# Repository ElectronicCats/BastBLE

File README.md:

# Bast BLE

Bast BLE is all the best in the world format Feather and BLE with a Nordic NRF!, Feather pin to pin compatible with a USB port type C.

Bast-BLE is supported in the Arduino development environment and Circuit Python coming soon

We love all our Feathers equally, but this Feather is very special. It's our first Feather that is specifically designed for use with CircuitPython! CircuitPython is our beginner-oriented flavor of MicroPython - and as the name hints at, its a small but full-featured version of the popular Python programming language specifically for use with circuitry and electronics.

Please note, CircuitPython does not come preloaded. See the full guide linked below for instructions on installing it

Lipoly battery and USB cable not included (but we do have lots of options in the shop if you'd like!)

## Hardware Features

* Nordic nRF52840 System-on-Chip
	- ARM® Cortex®-M4F processor optimized for ultra-low power operation
	- Combining *Bluetooth 5*, *Bluetooth Mesh*, *Thread*, *IEEE 802.15.4*, *ANT* and *2.4GHz proprietary*
	- On-chip NFC-A tag
	- On-chip USB 2.0 (Full speed) controller
	- ARM TrustZone® Cryptocell 310 security subsystem
	- 1 MB FLASH and 256 kB RAM
* Program/Debug options with DAPLink
	- MSC - drag-n-drop programming flash memory
	- CDC - virtual com port for log, trace and terminal emulation
	- HID - CMSIS-DAP compliant debug channel
	- WEBUSB HID - CMSIS-DAP compliant debug channel
* External ultra-low power 64-Mb QSPI FLASH memory
* Up to 21 GPIOs available via headers
* IF Boot/Reset Button
* On-board 2.4G chip antenna 
* 3.3V regulator with 1A peak current output
* VBUS & VIN Power-Path Management
* Reversible USB 3.1 Type-C Connector
* Breadboard-friendly with dual 18-Pin headers
* Feather Format

## How to get Bast BLE
Bast BLE is available on the following channels (click to go directly to the product):

## Pinout Diagram
Coming Soon..

## Software Resource

The nRF52840 Micro Dev Kit USB Dongle can be used to play with : *nRF5 SDK*, *OpenThread*, *Web Bluetooth*, *iBeacon*, *Eddystone*, and more.

| Software  | Brief Description |
| ---------- | ----- |
| [Arduino Core MbedOS](https://github.com/ElectronicCats/ArduinoCore-mbed) | The friendly Arduino core by Electronic Cats with MbedOS, |
| [UF2 Bootloader](https://github.com/ElectronicCats/Adafruit_nRF52_Bootloader) | UF2 Bootloader fir NRF52, |
| [nRF5 SDK](nrf5-sdk/) | Offical Software Development Kit for nRF51 and nRF52 Series |
| [OpenThread Border Router](OTBR/) | An open source border router, designed to work with OpenThread |
| [Thread Network Sniffer](thread-sniffer/) | Help you to efficiently analyze Thread network traffic|
| [Web Bluetooth](https://webbluetoothcg.github.io/web-bluetooth/) | Bluetooth support for the Web |
| [iBeacon](https://developer.apple.com/ibeacon/) | A Bluetooth low energy advertising message format designed by Apple |
| [Eddystone](https://github.com/google/eddystone) | A protocol specification that defines a Bluetooth low energy message format for proximity beacon messages |
| [CircuitPython](https://github.com/adafruit/circuitpython/blob/master/ports/nrf/README.md) | A Python language for microcontrollers designed to simplify experimentation and learning |
| [TinyGo](https://github.com/tinygo-org/tinygo) | Go compiler for small devices, based on LLVM |
| [Rust for nrf52840-mdk](https://github.com/nrf-rs/nrf52840-mdk-rs) | Rust support for the nrf52840-mdk development board |
| [RIOT OS](https://github.com/RIOT-OS/RIOT/blob/695e91a90a6545b6937bd0f52f0e87d278155ec0/boards/nrf52840-mdk/doc.txt) | The friendly Operating System for the Internet of Things, |

## Contributing

We would love for you to contribute to this project and help make it even better than it is today! 

License

Electronic Cats invests time and resources providing this open source design, please support Electronic Cats and open-source hardware by purchasing products from Electronic Cats!

Designed by Electronic Cats.

Firmware released under an GNU AGPL v3.0 license. See the LICENSE file for more information.

Hardware released under an CERN Open Hardware Licence v1.2. See the LICENSE_HARDWARE file for more information.

Electronic Cats is a registered trademark, please do not use if you sell these PCBs.

January 2020

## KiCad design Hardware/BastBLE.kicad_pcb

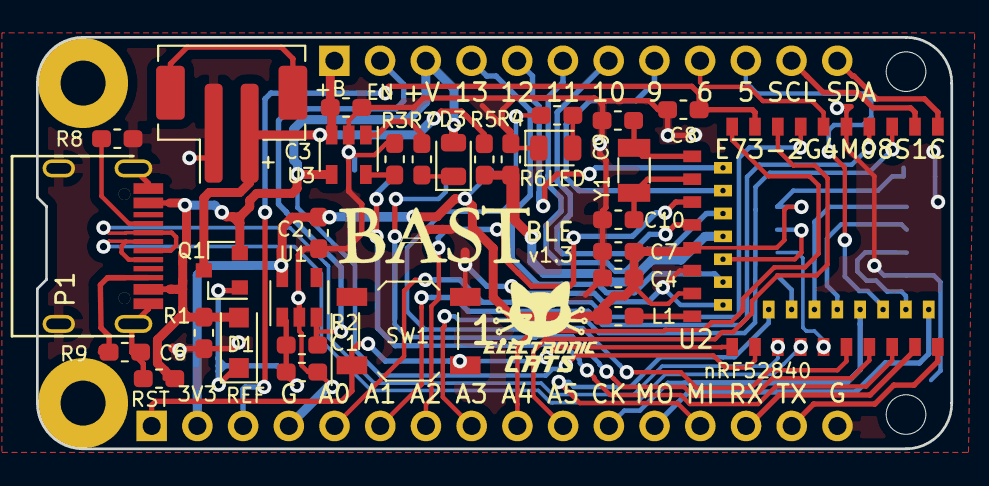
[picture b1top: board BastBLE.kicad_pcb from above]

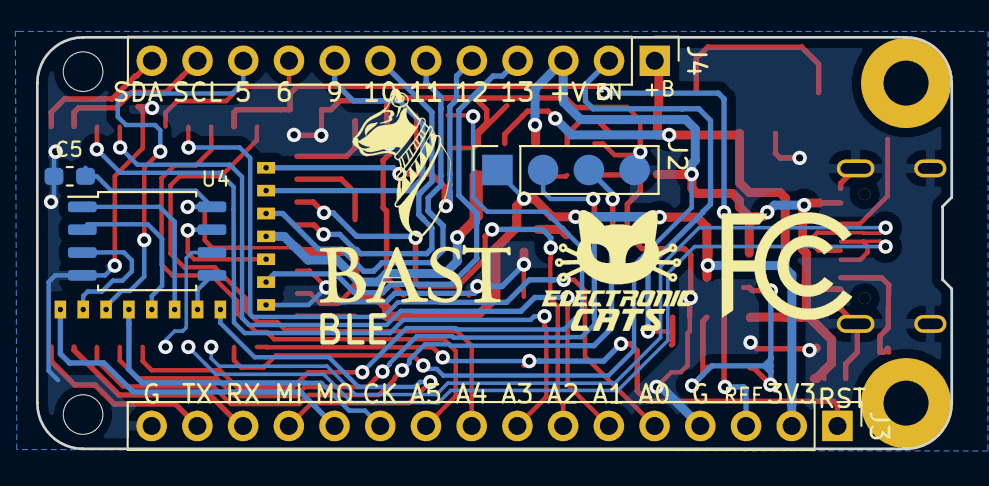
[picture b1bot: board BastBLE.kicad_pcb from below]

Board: 2 copper layers, 50.8 x 22.9 mm, 35 parts (5 on the bottom side), 49 nets.

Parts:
C1, C2, C3: 10uF; C_0603_1608Metric_Pad1.05x0.95mm_HandSolder
C4, C5, C6, C7, C8: 0.1uF; C_0603_1608Metric_Pad1.05x0.95mm_HandSolder
C9, C10: 22pF; C_0603_1608Metric_Pad1.05x0.95mm_HandSolder
D1: MBR120; D_SOD-123F
D2, D3: LED; LED_0805_2012Metric
J1: Conn_Battery; JST_PH_B2B-PH-SM4-TB_1x02-1MP_P2.00mm_Vertical
J2: SWD; PinSocket_1x04_P2.54mm_Vertical
J3: Conn_left; PinHeader_1x16_P2.54mm_Vertical
J4: Conn_right; PinHeader_1x12_P2.54mm_Vertical
L1: 10uH; L_0603_1608Metric_Pad1.05x0.95mm_HandSolder
P1: USB_C_Plug_USB2.0; C393939
Q1: DMG3415U-7; SOT-23
R1, R2, R5, R6: 100K; R_0603_1608Metric_Pad1.05x0.95mm_HandSolder
R3: 4K7; R_0603_1608Metric_Pad1.05x0.95mm_HandSolder
R4, R7: 1K; R_0603_1608Metric_Pad1.05x0.95mm_HandSolder
R8, R9: 5K1; R_0603_1608Metric_Pad1.05x0.95mm_HandSolder
SW1: RESET; SW_SPST_TL3342
U1: AP2112K-3.3; SOT-23-5
U2: E73-2G4M08S1C; E73-2G4M08S1C-52840
U3: MCP73831-2-OT; SOT-23-5
U4: W25Q32JVSS; SOIC-8_5.23x5.23mm_P1.27mm
Y1: 32Khz; Crystal_SMD_3215-2Pin_3.2x1.5mm

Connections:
+3V3: C2.1, C4.1, C5.1, C7.1, J2.1, J3.2, L1.1, U1.5, U2.19, U2.23, U4.8
+BATT: C3.2, J1.2, J4.1, Q1.3, R5.1, U3.3
/A0: J3.5, U2.7
/A1: J3.6, U2.4
/A2: J3.7, U2.15
/A3: J3.8, U2.3
/A4: J3.9, U2.10
/A5: J3.10, U2.8
/AREF: C8.1, J3.3, U2.9
/D5: J4.10, U2.38
/D6: J4.9, U2.6
/D9: J4.8, U2.14
/D10: J4.7, U2.17
/D11: J4.6, U2.16
/D12: J4.5, U2.12
/D13: J4.4, U2.22
/D+: P1.A6, U2.31
/D-: P1.A7, U2.29
/EN: J4.2, R2.2, U1.3
/LED: R4.1, U2.35
/MISO: J3.13, U2.28
/MOSI: J3.12, U2.42
/QSPI_CS: U2.32, U4.1
/QSPI_DATA0: U2.30, U4.5
/QSPI_DATA1: U2.34, U4.2
/QSPI_DATA2: U2.40, U4.3
/QSPI_DATA3: U2.20, U4.7
/QSPI_SCK: U2.33, U4.6
/RST: J3.1, SW1.2, U2.26
/RX: J3.14, U2.41
/SCK: J3.11, U2.36
/SCL: J4.11, U2.2
/SDA: J4.12, U2.1
/SWCLK: J2.3, U2.39
/SWDIO: J2.2, U2.37
/TX: J3.15, U2.43
/VBAT: R5.2, R6.1, U2.18
GND: C1.2, C2.2, C3.1, C4.2, C5.2, C6.2, C7.2, C8.2, C9.2, C10.2, D2.1, J1.1, J2.4, J3.4, J3.16, P1.A1, P1.S1, R1.2, R3.2, R6.2, R8.1, R9.1, SW1.1, U1.2, U2.5, U2.21, U2.24, U3.2, U4.4
unnamed: C1.1, D1.1, Q1.1, R2.1, U1.1
unnamed: C9.1, U2.11, Y1.1
unnamed: C10.1, U2.13, Y1.2
unnamed: D2.2, R4.2
unnamed: D3.1, R7.1
unnamed: L1.2, U2.25
unnamed: P1.A5, R8.2
unnamed: P1.B5, R9.2
unnamed: R3.1, U3.5
unnamed: R7.2, U3.1
VBUS: C6.1, D1.2, D3.2, J4.3, P1.A4, Q1.2, R1.1, U2.27, U3.4

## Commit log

2020-01-23 schematic
2020-01-23 add gitignore
2020-02-01 assigned pinout complete
2020-02-01 SWD pinout ok, assigned mosfet
2020-02-09 Format adafruit in PCB, init BOM
2020-02-11 init assignament footprints
2020-02-19 Review PCB
2020-03-14 change L1 package
2020-03-26 fix failed components and tracks
2020-03-27 routeo signals
2020-03-28 Communication miso, mosi, tx, rx
2020-03-30 Routeo a4 a5, fix sck mosi
2020-03-30 fix c8, r6, and pin
2020-03-31 D11-SDA
2020-04-14 change pins schematic
2020-04-15 change routeo
2020-04-20 routeo D
2020-04-22 chenge analog signals routeo
2020-04-23 A0 rf
2020-04-24 erase traces, add note
2020-04-24 add crystal and fix analogs
2020-05-04 add footprint and netlist
2020-05-05 fix components
2020-05-05 C6 VBUS
2020-05-06 D- D+
2020-05-07 Flash memory
2020-05-07 change pin SDA SCL
2020-05-08 fix traces
2020-05-08 tracks u2
2020-05-08 VBUS and batt
2020-05-12 A1 change cap vbus
2020-05-12 tracks y1
2020-05-20 first routing
2020-05-20 added logos and pinout
2020-05-20 label 6 fix
2020-05-21 fix groudn traces and labels
2020-05-21 add manf# to crystal
2020-06-15 Manf#
2020-07-11 VBA and D12 exchanged and routed.
2020-07-11 fix logo and connector swd
2020-07-14 AREF routed
2020-07-16 Add logos fix gnd
2020-07-19 change memory GD25Q16C
2020-07-27 Ground label fixed
2020-09-22 Update link for Mbed Core
2021-01-08 firs code
2021-01-14 ble incorporation
2021-01-14 Added datasheet
2021-01-18 app code
2021-01-20 Create LICENSE_HARDWARE
2021-01-23 error in app fixed and actualization of the code for arduino
2021-02-04 memori recording and actualization of the app
2021-04-01 Update apk android
    New App for project robot arm BLE
2021-04-06 add folder example
2022-09-29 added the issue template
